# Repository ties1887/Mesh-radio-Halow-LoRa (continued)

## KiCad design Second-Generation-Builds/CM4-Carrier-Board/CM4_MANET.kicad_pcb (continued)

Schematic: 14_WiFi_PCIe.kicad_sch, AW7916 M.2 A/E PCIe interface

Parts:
C400: 100n / 16V; C_0603_1608Metric; MPN CL10B104KB8NNNC; LCSC C1591
J400: APCI0085-P005A / M.2 E-key socket; M2_E_KEY_APCI0085-P005A; MPN APCI0085-P005A; LCSC C7498138
R400, R401: 10k; R_0603_1608Metric; MPN 0603WAF1002T5E; LCSC C25804
R402: 10k / host-domain pullup; R_0603_1608Metric; MPN 0603WAF1002T5E; LCSC C25804
U400: 74LVC1G07SE-7; SOT-353_SC-70-5; MPN 74LVC1G07SE-7; LCSC C67531

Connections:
+3V3_CM4: R402.1; also elsewhere on the board
+3V3_WIFI: C400.1, J400.2 (3V3), J400.4 (3V3), J400.72 (3V3), J400.74 (3V3), R400.1, R401.1, U400.5 (VCC); also elsewhere on the board
CM4_PCIE_RST_N: U400.2 (A); also elsewhere on the board
GND: C400.2, J400.1 (GND), J400.7 (GND), J400.18 (GND), J400.33 (GND), J400.39 (GND), J400.45 (GND), J400.51 (GND), J400.57 (GND), J400.63 (GND), J400.69 (GND), J400.75 (GND), U400.3 (GND); also elsewhere on the board
PCIE_CLKREQ_N: J400.53 (CLKREQ_N), R402.2; also elsewhere on the board
PCIE_CLK_N: J400.49 (REFCLK_N); also elsewhere on the board
PCIE_CLK_P: J400.47 (REFCLK_P); also elsewhere on the board
PCIE_RX_N: J400.43 (CARD_TX_N); also elsewhere on the board
PCIE_RX_P: J400.41 (CARD_TX_P); also elsewhere on the board
PCIE_TX_N: J400.37 (CARD_RX_N); also elsewhere on the board
PCIE_TX_P: J400.35 (CARD_RX_P); also elsewhere on the board
WIFI_ENABLE_N: J400.56 (W_DISABLE1_N), R401.2
WIFI_PERST_N: J400.52 (PERST_N), R400.2, U400.4 (Y)

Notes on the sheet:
All four power contacts (2,4,72,74) carry WiFi supply; connector must support at least 0.75 A per power contact.
CM4 already includes PCIe TX and REFCLK coupling. Confirm coupling on AW7916 TX before PCB release.
AsiaRF drawing names TX/RX from card perspective: card RX pins35/37 receive CM4 TX; card TX41/43 drive CM4 RX.
Exact 1A/contact E-key socket suffix, physical mating and footprint are release blockers. Generic 0.5A sockets rejected.

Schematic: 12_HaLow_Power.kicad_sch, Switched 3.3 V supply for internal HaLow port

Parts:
C260: 1u / 10V input; C_0603_1608Metric; MPN CL10A105KB8NNNC; LCSC C15849
R260: 26.1k / 1%; R_0603_1608Metric; MPN FRC0603F2612TS; LCSC C2933182
R261, R262: 100k; R_0603_1608Metric; MPN 0603WAF1003T5E; LCSC C25803
R263: 10k / discharge; R_0603_1608Metric; MPN 0603WAF1002T5E; LCSC C25804
TP260: +3V3_HALOW; TestPoint_Pad_D1.5mm; JLCPCB Status EXCLUDE_FROM_JLCPCB_ASSEMBLY
U260: TPS2553DBVR; SOT-23-6; MPN TPS2553DBVR; LCSC C55266

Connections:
+3V3_AUX: C260.1, R262.1, U260.1 (IN); also elsewhere on the board
+3V3_HALOW: R263.1, TP260.1, U260.6 (OUT); also elsewhere on the board
GND: C260.2, R260.2, R261.2, R263.2, U260.2 (GND); also elsewhere on the board
HALOW_EN: R261.1, U260.3 (EN); also elsewhere on the board
HALOW_FAULT_N: R262.2, U260.4 (FAULT_N); also elsewhere on the board
HALOW_ILIM: R260.1, U260.5 (ILIM)

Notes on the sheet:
Internal hub port 1 enables the HaLow supply. This is a 3.3 V embedded-device rail, not external USB VBUS.
The whole module, including VDDIO and VDD_USB, powers from the same switched rail.
TPS2553 26.1k/1% limit: 908-1081mA, nominal 989mA; design reservation 0.6 A pending peak measurement.
RESET RC is on HaLow sheet. Check turn-off discharge/re-enumeration and 3.0 V minimum at module under peak load.

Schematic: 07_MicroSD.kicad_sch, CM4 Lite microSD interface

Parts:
C120: 10u / 10V; C_0805_2012Metric; MPN CL21A106KAYNNNE; LCSC C15850
C121: 100n / 16V; C_0603_1608Metric; MPN CL10B104KB8NNNC; LCSC C1591
J120: Molex 5033981892; SDCARD_MOLEX_503398-1892; MPN 5033981892; LCSC C428492
R120: 12k / 1%; R_0603_1608Metric; MPN FRC0603F1202TS; LCSC C2906989
U120: RT9742GGJ5; SOT-23-5; MPN RT9742GGJ5; LCSC C250547

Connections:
+3V3_CM4: C121.1, R120.1, U120.5 (VIN); also elsewhere on the board
GND: C120.2, C121.2, J120.6 (VSS), J120.11 (SHIELD), U120.2 (GND); also elsewhere on the board
SD_CLK: J120.5 (CLK); also elsewhere on the board
SD_CMD: J120.3 (CMD); also elsewhere on the board
SD_DAT0: J120.7 (DAT0); also elsewhere on the board
SD_DAT1: J120.8 (DAT1); also elsewhere on the board
SD_DAT2: J120.1 (DAT2); also elsewhere on the board
SD_DAT3: J120.2 (DAT3); also elsewhere on the board
SD_PWR_ON: R120.2, U120.4 (EN); also elsewhere on the board
SD_VDD: C120.1, J120.4 (VDD), U120.1 (VOUT)

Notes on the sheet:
Molex 503398-1892 socket and switched 3.3 V follow CM4IO reference.
Keep SD traces short with uninterrupted ground reference. 32 GB U3 card supplied separately.
No external pull-ups on SD data/CMD: use the CM4 reference arrangement. Card detect unused.
SD_PWR_ON has a pull-up so card is powered during boot. SD_VDD_OVERRIDE remains unconnected on CM4.

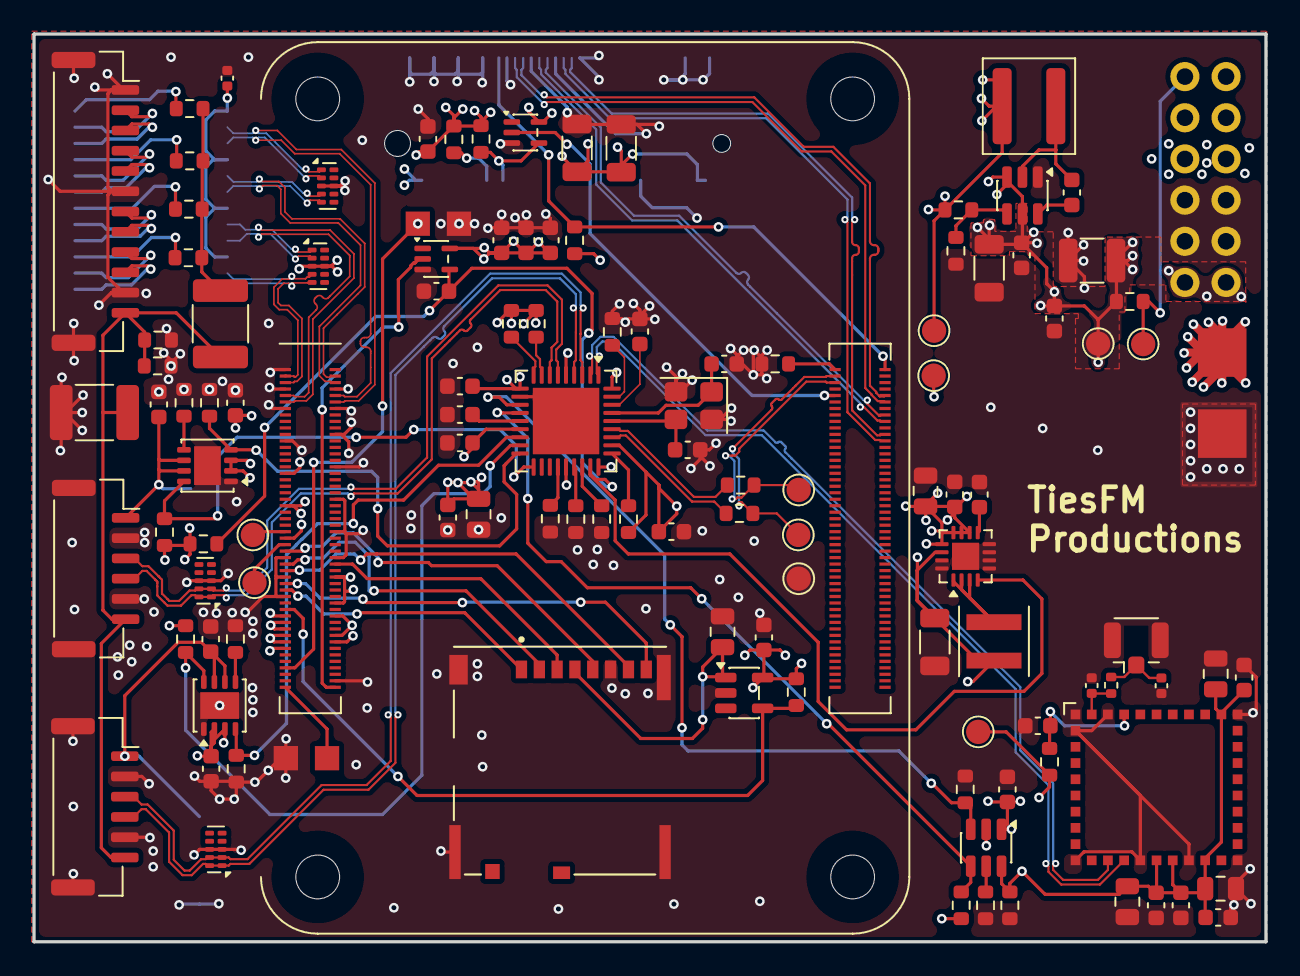
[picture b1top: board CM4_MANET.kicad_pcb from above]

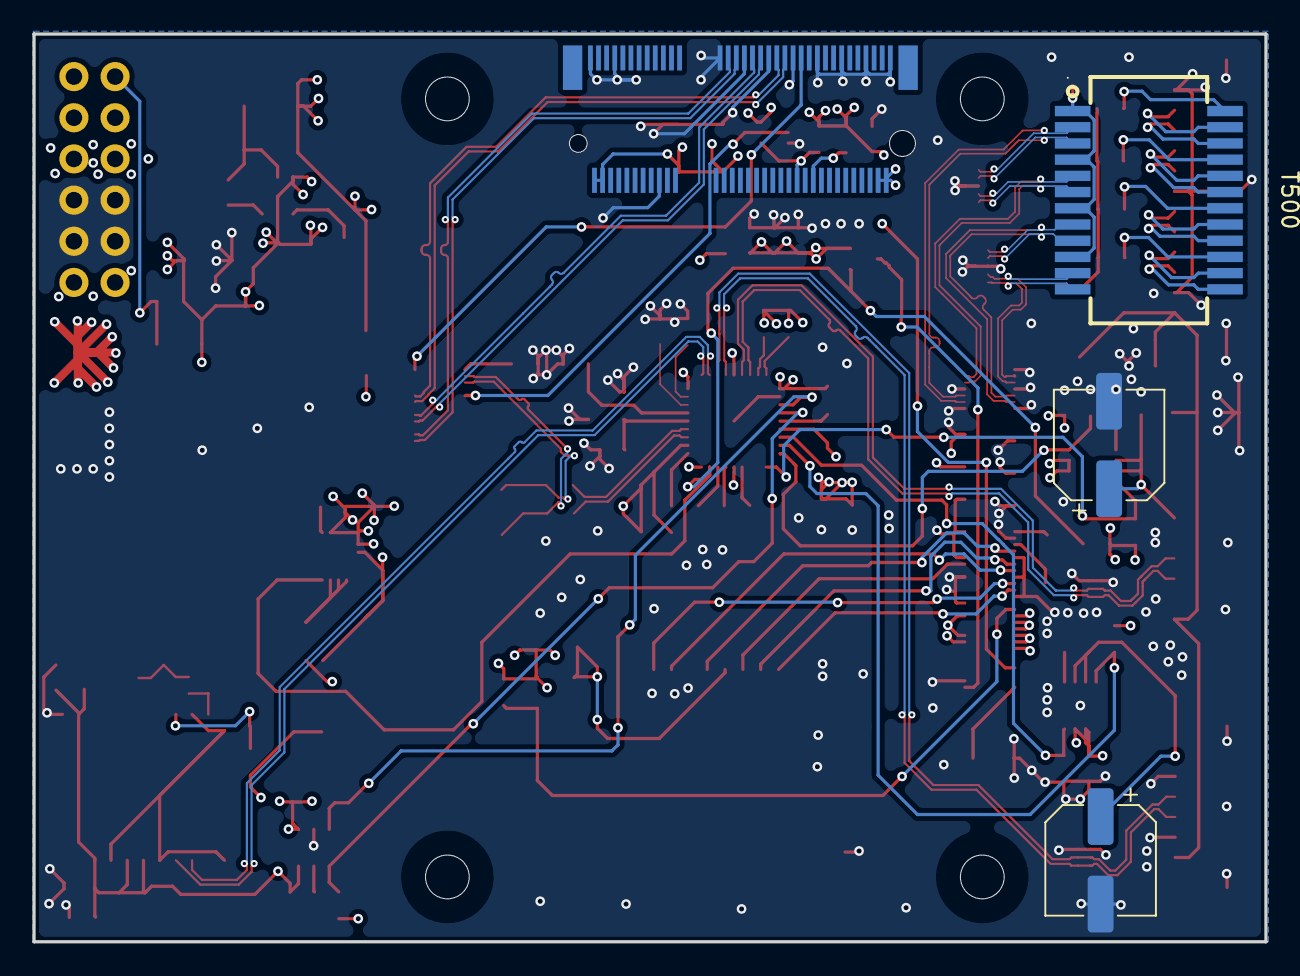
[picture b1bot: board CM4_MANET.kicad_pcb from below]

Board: 6 copper layers, 76.0 x 56.0 mm, 122 parts (4 on the bottom side), 96 nets.

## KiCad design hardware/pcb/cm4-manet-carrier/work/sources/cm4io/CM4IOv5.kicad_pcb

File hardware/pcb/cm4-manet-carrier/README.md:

# CM4 MANET — GitHub/Hermes-overdracht

Lees eerst HERMES-OVERDRACHT.md. Deze map wordt na de door de gebruiker gevraagde import in zijn GitHub-repository de centrale projectbron. Repository-URL en succesvolle upload zijn hier nog niet bekend. Deze overdracht uploadt zelf niets.

**Nieuwste proef: v0.8, AFGEKEURD. Referentie: v0.7, ook nog NIET geschikt voor productie. Geen gerouteerd carrierbord of vrijgegeven Gerbers.**

Alle historische versies, beschikbare lokale bronnen, modellen, scripts en projectnotities zijn behouden, behalve lokale caches, sessie-instellingen en interne Gitgeschiedenis. Het is geen volledige chat-export. Actuele aanwijzingen in dit README en HERMES-OVERDRACHT gaan vóór verouderde status-/Nextcloud-/routingstopteksten in historische documenten.

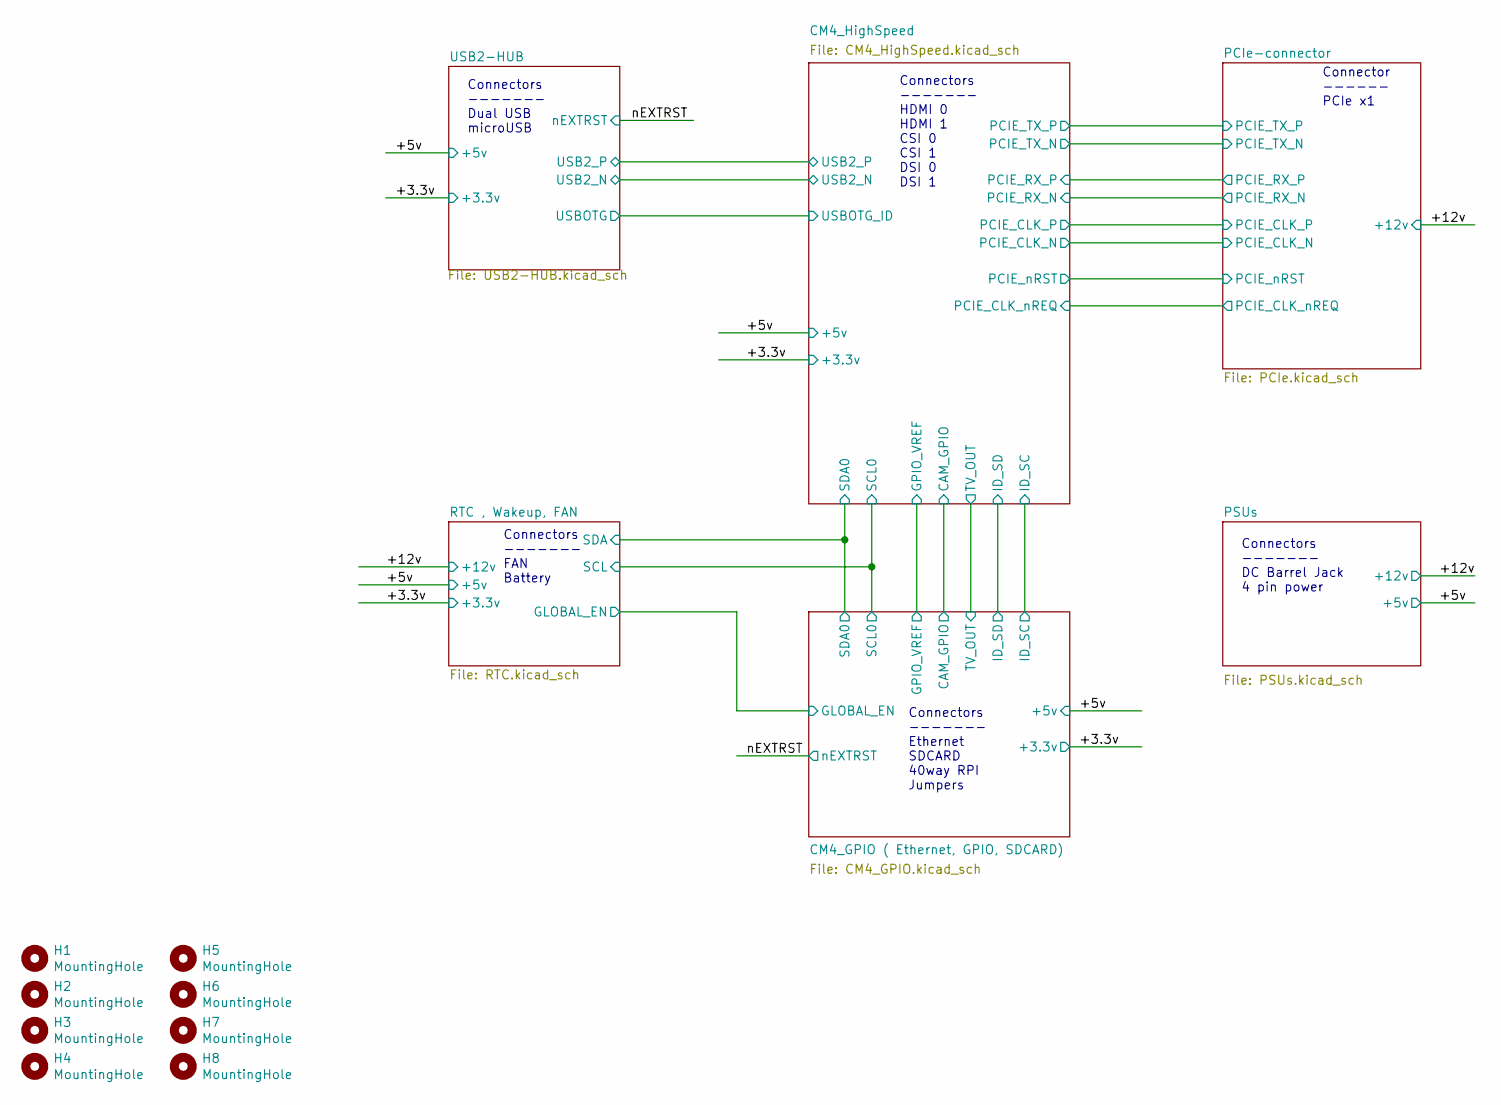
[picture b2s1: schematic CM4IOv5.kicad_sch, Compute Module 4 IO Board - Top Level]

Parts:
H1, H2, H3, H4, H5, H6, H7, H8: MountingHole; MountingHole_2.7mm_M2.5; Part Description M2.5 mounting hole

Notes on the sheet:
Connectors ------- FAN Battery
Connector ------ PCIe x1
Connectors ------- DC Barrel Jack 4 pin power
Connectors ------- Dual USB microUSB
Connectors ------- Ethernet SDCARD 40way RPI Jumpers
Connectors ------- HDMI 0 HDMI 1 CSI 0 CSI 1 DSI 0 DSI 1

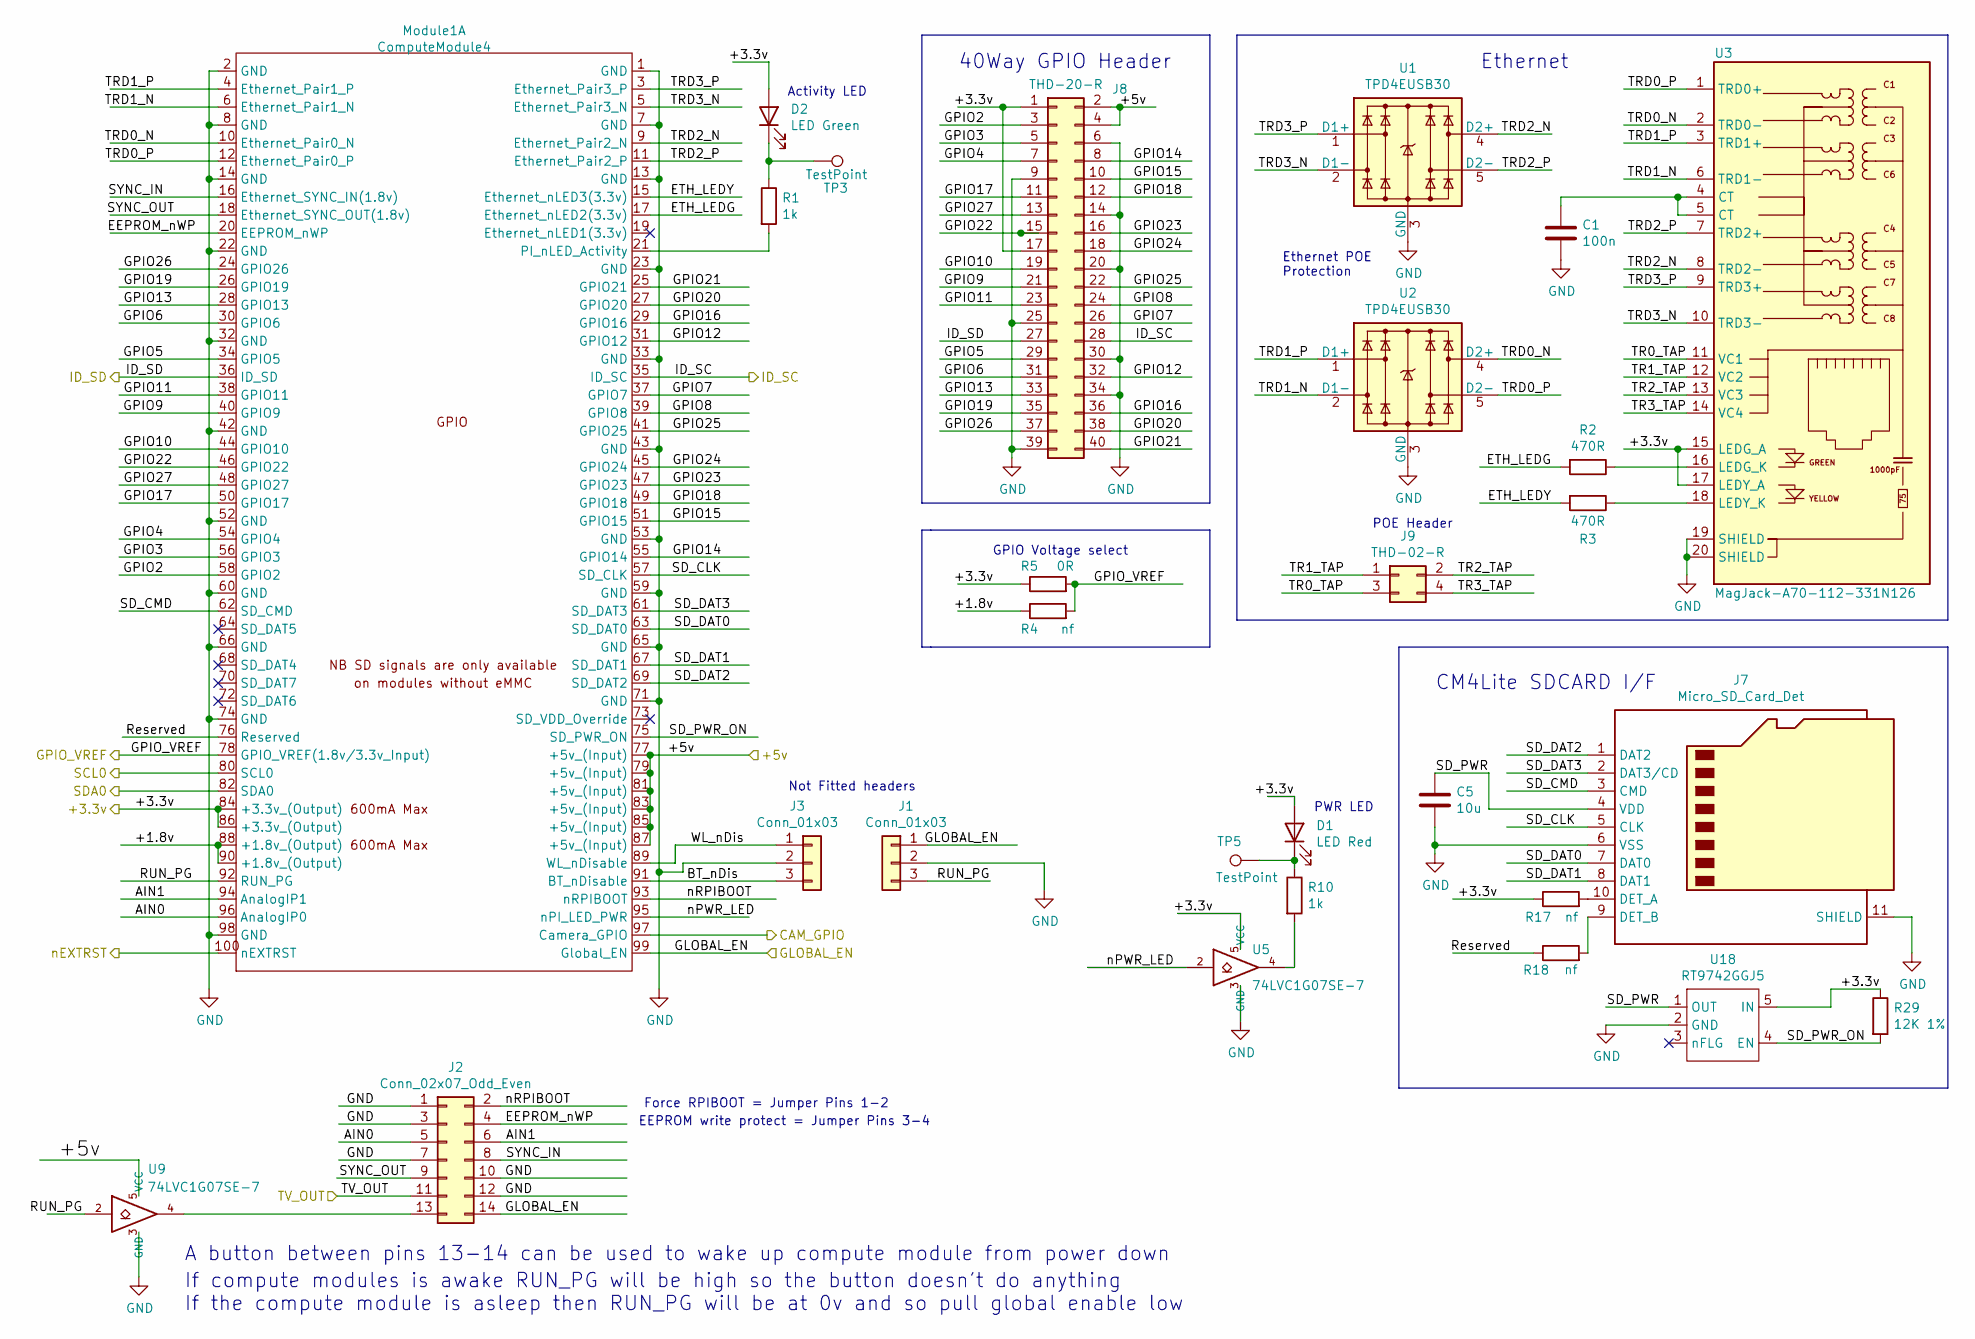
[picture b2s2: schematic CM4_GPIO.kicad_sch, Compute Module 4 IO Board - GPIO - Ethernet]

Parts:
C1: 100n; C_0402_1005Metric; Part Description 0.1uF 10% 16V Ceramic Capacitor X7R 040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
C5: 10u; C_0805_2012Metric; Part Description 10uF 10% 10V Ceramic Capacitor X7R 0805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
D1: LED Red; LED_0603_1608Metric; Part Description Red 620nm LED Indication - Discrete 2.2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
D2: LED Green; LED_0603_1608Metric; Part Description Green 572nm LED Indication - Discrete 2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
J1, J3: Conn_01x03; PinHeader_1x03_P2.54mm_Vertical; Part Description 3pin 0.1" connector
J2: Conn_02x07_Odd_Even; PinHeader_2x07_P2.54mm_Vertical; Part Description PinHeader_2x07_P2.54mm_Vertical
J7: Micro_SD_Card_Det; SDCARD_MOLEX_503398-1892; Part Description 9 (8 + 1) Position Card Connector micro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
J8: THD-20-R; PinHeader_2x20_P2.54mm_Vertical; Part Description PinHeader_2x20_P2.54mm_Vertical
J9: THD-02-R; PinHeader_2x02_P2.54mm_Vertical; Part Description PinHeader_2x02_P2.54mm_Vertical
Module1: ComputeModule4; Raspberry-Pi-4-Compute-Module; Part Description 100 Position Connector Receptacle, Cent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
R1, R10: 1k; R_0402_1005Metric; Part Description Resistor 1K M1005 1% 63mW
R2, R3: 470R; R_0402_1005Metric; Part Description Resistor 470R M1005 1% 63mW
R4: nf; R_0805_2012Metric_Pad1.15x1.40mm_HandSolder
R5: 0R; R_0805_2012Metric_Pad1.15x1.40mm_HandSolder; Part Description Resistor 0R M2012 5%
R17, R18: nf; R_0402_1005Metric; Part Description Resistor 1K M1005 1% 63mW
R29: 12K 1%; R_0402_1005Metric; Part Description Resistor 12K M1005 1% 63mW
TP3, TP5: TestPoint; TestPoint_Pad_2.0x2.0mm
U1, U2: TPD4EUSB30; USON-10_2.5x1.0mm_P0.5mm; Part Description Quad TVS diode for high speed signals (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
U3: MagJack-A70-112-331N126; TRJG0926HENL; Part Description Gigabit Ethernet Magjack
U5, U9: 74LVC1G07SE-7; SOT-353_SC-70-5; Part Description Buffer, Non-Inverting 1 Element 1 Bit p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
U18: RT9742GGJ5; SOT-23-5; Part Description Power Switch/Driver 1:1 N-Channel 1A TS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

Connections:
/+3.3v: D1.2 (A), D2.2 (A), J8.1, J8.17, Module1.84 (+3.3v_(Output)), Module1.86 (+3.3v_(Output)), R5.1, R17.1, R29.1, U3.15 (LEDG_A), U3.17 (LEDY_A), U5.5 (VCC), U18.5 (IN); also elsewhere on the board
/+5v: J8.2, J8.4, Module1.77 (+5v_(Input)), Module1.79 (+5v_(Input)), Module1.81 (+5v_(Input)), Module1.83 (+5v_(Input)), Module1.85 (+5v_(Input)), Module1.87 (+5v_(Input)), U9.5 (VCC); also elsewhere on the board
/CM4_GPIO ( Ethernet, GPIO, SDCARD)/+1.8v: Module1.88 (+1.8v_(Output)), Module1.90 (+1.8v_(Output)), R4.1
/CM4_GPIO ( Ethernet, GPIO, SDCARD)/AIN0: J2.5, Module1.96 (AnalogIP0)
/CM4_GPIO ( Ethernet, GPIO, SDCARD)/AIN1: J2.6, Module1.94 (AnalogIP1)
/CM4_GPIO ( Ethernet, GPIO, SDCARD)/BT_nDis: J3.3, Module1.91 (BT_nDisable)
/CM4_GPIO ( Ethernet, GPIO, SDCARD)/EEPROM_nWP: J2.4, Module1.20 (EEPROM_nWP)
/CM4_GPIO ( Ethernet, GPIO, SDCARD)/ETH_LEDG: Module1.17 (Ethernet_nLED2(3.3v)), R2.2
/CM4_GPIO ( Ethernet, GPIO, SDCARD)/ETH_LEDY: Module1.15 (Ethernet_nLED3(3.3v)), R3.2
/CM4_GPIO ( Ethernet, GPIO, SDCARD)/GLOBAL_EN: J1.1, J2.14, Module1.99 (Global_EN); also elsewhere on the board
/CM4_GPIO ( Ethernet, GPIO, SDCARD)/GPIO2: J8.3, Module1.58 (GPIO2)
/CM4_GPIO ( Ethernet, GPIO, SDCARD)/GPIO3: J8.5, Module1.56 (GPIO3)
/CM4_GPIO ( Ethernet, GPIO, SDCARD)/GPIO4: J8.7, Module1.54 (GPIO4)
/CM4_GPIO ( Ethernet, GPIO, SDCARD)/GPIO5: J8.29, Module1.34 (GPIO5)
/CM4_GPIO ( Ethernet, GPIO, SDCARD)/GPIO6: J8.31, Module1.30 (GPIO6)
/CM4_GPIO ( Ethernet, GPIO, SDCARD)/GPIO7: J8.26, Module1.37 (GPIO7)
/CM4_GPIO ( Ethernet, GPIO, SDCARD)/GPIO8: J8.24, Module1.39 (GPIO8)
/CM4_GPIO ( Ethernet, GPIO, SDCARD)/GPIO9: J8.21, Module1.40 (GPIO9)
/CM4_GPIO ( Ethernet, GPIO, SDCARD)/GPIO10: J8.19, Module1.44 (GPIO10)
/CM4_GPIO ( Ethernet, GPIO, SDCARD)/GPIO11: J8.23, Module1.38 (GPIO11)
/CM4_GPIO ( Ethernet, GPIO, SDCARD)/GPIO12: J8.32, Module1.31 (GPIO12)
/CM4_GPIO ( Ethernet, GPIO, SDCARD)/GPIO13: J8.33, Module1.28 (GPIO13)
/CM4_GPIO ( Ethernet, GPIO, SDCARD)/GPIO14: J8.8, Module1.55 (GPIO14)
/CM4_GPIO ( Ethernet, GPIO, SDCARD)/GPIO15: J8.10, Module1.51 (GPIO15)
/CM4_GPIO ( Ethernet, GPIO, SDCARD)/GPIO16: J8.36, Module1.29 (GPIO16)
/CM4_GPIO ( Ethernet, GPIO, SDCARD)/GPIO17: J8.11, Module1.50 (GPIO17)
/CM4_GPIO ( Ethernet, GPIO, SDCARD)/GPIO18: J8.12, Module1.49 (GPIO18)
/CM4_GPIO ( Ethernet, GPIO, SDCARD)/GPIO19: J8.35, Module1.26 (GPIO19)
/CM4_GPIO ( Ethernet, GPIO, SDCARD)/GPIO20: J8.38, Module1.27 (GPIO20)
/CM4_GPIO ( Ethernet, GPIO, SDCARD)/GPIO21: J8.40, Module1.25 (GPIO21)
/CM4_GPIO ( Ethernet, GPIO, SDCARD)/GPIO22: J8.15, Module1.46 (GPIO22)
/CM4_GPIO ( Ethernet, GPIO, SDCARD)/GPIO23: J8.16, Module1.47 (GPIO23)
/CM4_GPIO ( Ethernet, GPIO, SDCARD)/GPIO24: J8.18, Module1.45 (GPIO24)
/CM4_GPIO ( Ethernet, GPIO, SDCARD)/GPIO25: J8.22, Module1.41 (GPIO25)
/CM4_GPIO ( Ethernet, GPIO, SDCARD)/GPIO26: J8.37, Module1.24 (GPIO26)
/CM4_GPIO ( Ethernet, GPIO, SDCARD)/GPIO27: J8.13, Module1.48 (GPIO27)
/CM4_GPIO ( Ethernet, GPIO, SDCARD)/GPIO_VREF: Module1.78 (GPIO_VREF(1.8v/3.3v_Input)), R4.2, R5.2; also elsewhere on the board
/CM4_GPIO ( Ethernet, GPIO, SDCARD)/ID_SC: J8.28, Module1.35 (ID_SC); also elsewhere on the board
/CM4_GPIO ( Ethernet, GPIO, SDCARD)/ID_SD: J8.27, Module1.36 (ID_SD); also elsewhere on the board
/CM4_GPIO ( Ethernet, GPIO, SDCARD)/RUN_PG: J1.3, Module1.92 (RUN_PG), U9.2
/CM4_GPIO ( Ethernet, GPIO, SDCARD)/Reserved: Module1.76 (Reserved), R18.1
/CM4_GPIO ( Ethernet, GPIO, SDCARD)/SD_CLK: J7.5 (CLK), Module1.57 (SD_CLK)
/CM4_GPIO ( Ethernet, GPIO, SDCARD)/SD_CMD: J7.3 (CMD), Module1.62 (SD_CMD)
/CM4_GPIO ( Ethernet, GPIO, SDCARD)/SD_DAT0: J7.7 (DAT0), Module1.63 (SD_DAT0)
/CM4_GPIO ( Ethernet, GPIO, SDCARD)/SD_DAT1: J7.8 (DAT1), Module1.67 (SD_DAT1)
/CM4_GPIO ( Ethernet, GPIO, SDCARD)/SD_DAT2: J7.1 (DAT2), Module1.69 (SD_DAT2)
/CM4_GPIO ( Ethernet, GPIO, SDCARD)/SD_DAT3: J7.2 (DAT3/CD), Module1.61 (SD_DAT3)
/CM4_GPIO ( Ethernet, GPIO, SDCARD)/SD_PWR: C5.1, J7.4 (VDD), U18.1 (OUT)
/CM4_GPIO ( Ethernet, GPIO, SDCARD)/SD_PWR_ON: Module1.75 (SD_PWR_ON), R29.2, U18.4 (EN)
/CM4_GPIO ( Ethernet, GPIO, SDCARD)/SYNC_IN: J2.8, Module1.16 (Ethernet_SYNC_IN(1.8v))
/CM4_GPIO ( Ethernet, GPIO, SDCARD)/SYNC_OUT: J2.9, Module1.18 (Ethernet_SYNC_OUT(1.8v))
/CM4_GPIO ( Ethernet, GPIO, SDCARD)/TR0_TAP: J9.3, U3.11 (VC1)
/CM4_GPIO ( Ethernet, GPIO, SDCARD)/TR1_TAP: J9.1, U3.12 (VC2)
/CM4_GPIO ( Ethernet, GPIO, SDCARD)/TR2_TAP: J9.2, U3.13 (VC3)
/CM4_GPIO ( Ethernet, GPIO, SDCARD)/TR3_TAP: J9.4, U3.14 (VC4)
/CM4_GPIO ( Ethernet, GPIO, SDCARD)/TRD0_N: Module1.10 (Ethernet_Pair0_N), U2.4 (D2+), U2.7, U3.2 (TRD0-)
/CM4_GPIO ( Ethernet, GPIO, SDCARD)/TRD0_P: Module1.12 (Ethernet_Pair0_P), U2.5 (D2-), U2.6, U3.1 (TRD0+)
/CM4_GPIO ( Ethernet, GPIO, SDCARD)/TRD1_N: Module1.6 (Ethernet_Pair1_N), U2.2 (D1-), U2.9, U3.6 (TRD1-)
/CM4_GPIO ( Ethernet, GPIO, SDCARD)/TRD1_P: Module1.4 (Ethernet_Pair1_P), U2.1 (D1+), U2.10, U3.3 (TRD1+)
/CM4_GPIO ( Ethernet, GPIO, SDCARD)/TRD2_N: Module1.9 (Ethernet_Pair2_N), U1.4 (D2+), U1.7, U3.8 (TRD2-)
/CM4_GPIO ( Ethernet, GPIO, SDCARD)/TRD2_P: Module1.11 (Ethernet_Pair2_P), U1.5 (D2-), U1.6, U3.7 (TRD2+)
/CM4_GPIO ( Ethernet, GPIO, SDCARD)/TRD3_N: Module1.5 (Ethernet_Pair3_N), U1.2 (D1-), U1.9, U3.10 (TRD3-)
/CM4_GPIO ( Ethernet, GPIO, SDCARD)/TRD3_P: Module1.3 (Ethernet_Pair3_P), U1.1 (D1+), U1.10, U3.9 (TRD3+)
/CM4_GPIO ( Ethernet, GPIO, SDCARD)/TV_OUT: J2.11; also elsewhere on the board
/CM4_GPIO ( Ethernet, GPIO, SDCARD)/WL_nDis: J3.1, Module1.89 (WL_nDisable)
/CM4_GPIO ( Ethernet, GPIO, SDCARD)/nPWR_LED: Module1.95 (nPI_LED_PWR), U5.2
/CM4_GPIO ( Ethernet, GPIO, SDCARD)/nRPIBOOT: J2.2, Module1.93 (nRPIBOOT)
/CM4_HighSpeed/CAM_GPIO: Module1.97 (Camera_GPIO); also elsewhere on the board
/CM4_HighSpeed/SCL0: Module1.80 (SCL0); also elsewhere on the board
/CM4_HighSpeed/SDA0: Module1.82 (SDA0); also elsewhere on the board
/nEXTRST: Module1.100 (nEXTRST); also elsewhere on the board
GND: C1.2, C5.2, J1.2, J2.1, J2.3, J2.7, J2.10, J2.12, J3.2, J7.6 (VSS), J7.11 (SHIELD), J8.6, J8.9, J8.14, J8.20, J8.25, J8.30, J8.34, J8.39, Module1.1 (GND), Module1.2 (GND), Module1.7 (GND), Module1.8 (GND), Module1.13 (GND), Module1.14 (GND), Module1.22 (GND), Module1.23 (GND), Module1.32 (GND), Module1.33 (GND), Module1.42 (GND), Module1.43 (GND), Module1.52 (GND), Module1.53 (GND), Module1.59 (GND), Module1.60 (GND), Module1.65 (GND), Module1.66 (GND), Module1.71 (GND), Module1.74 (GND), Module1.98 (GND), U1.3 (GND), U1.8 (GND), U2.3 (GND), U2.8 (GND), U3.19 (SHIELD), U3.20 (SHIELD), U5.3 (GND), U9.3 (GND), U18.2 (GND); also elsewhere on the board
unnamed: C1.1, U3.4 (CT), U3.5 (CT)
unnamed: D1.1 (K), R10.1, TP5.1
unnamed: D2.1 (K), R1.1, TP3.1
unnamed: J2.13, U9.4
unnamed: J7.9 (DET_B), R18.2
unnamed: J7.10 (DET_A), R17.2
unnamed: Module1.21 (PI_nLED_Activity), R1.2
unnamed: R2.1, U3.16 (LEDG_K)
unnamed: R3.1, U3.18 (LEDY_K)
unnamed: R10.2, U5.4

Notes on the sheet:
PWR LED
Ethernet POE Protection
40Way GPIO Header
CM4Lite SDCARD I/F
GPIO Voltage select
Ethernet
Activity LED
EEPROM write protect = Jumper Pins 3-4
Not Fitted headers
A button between pins 13-14 can be used to wake up compute module from power down
If compute modules is awake RUN_PG will be high so the button doesn't do anything If the compute module is asleep then RUN_PG will be at 0v and so pull global enable low
Force RPIBOOT = Jumper Pins 1-2
POE Header

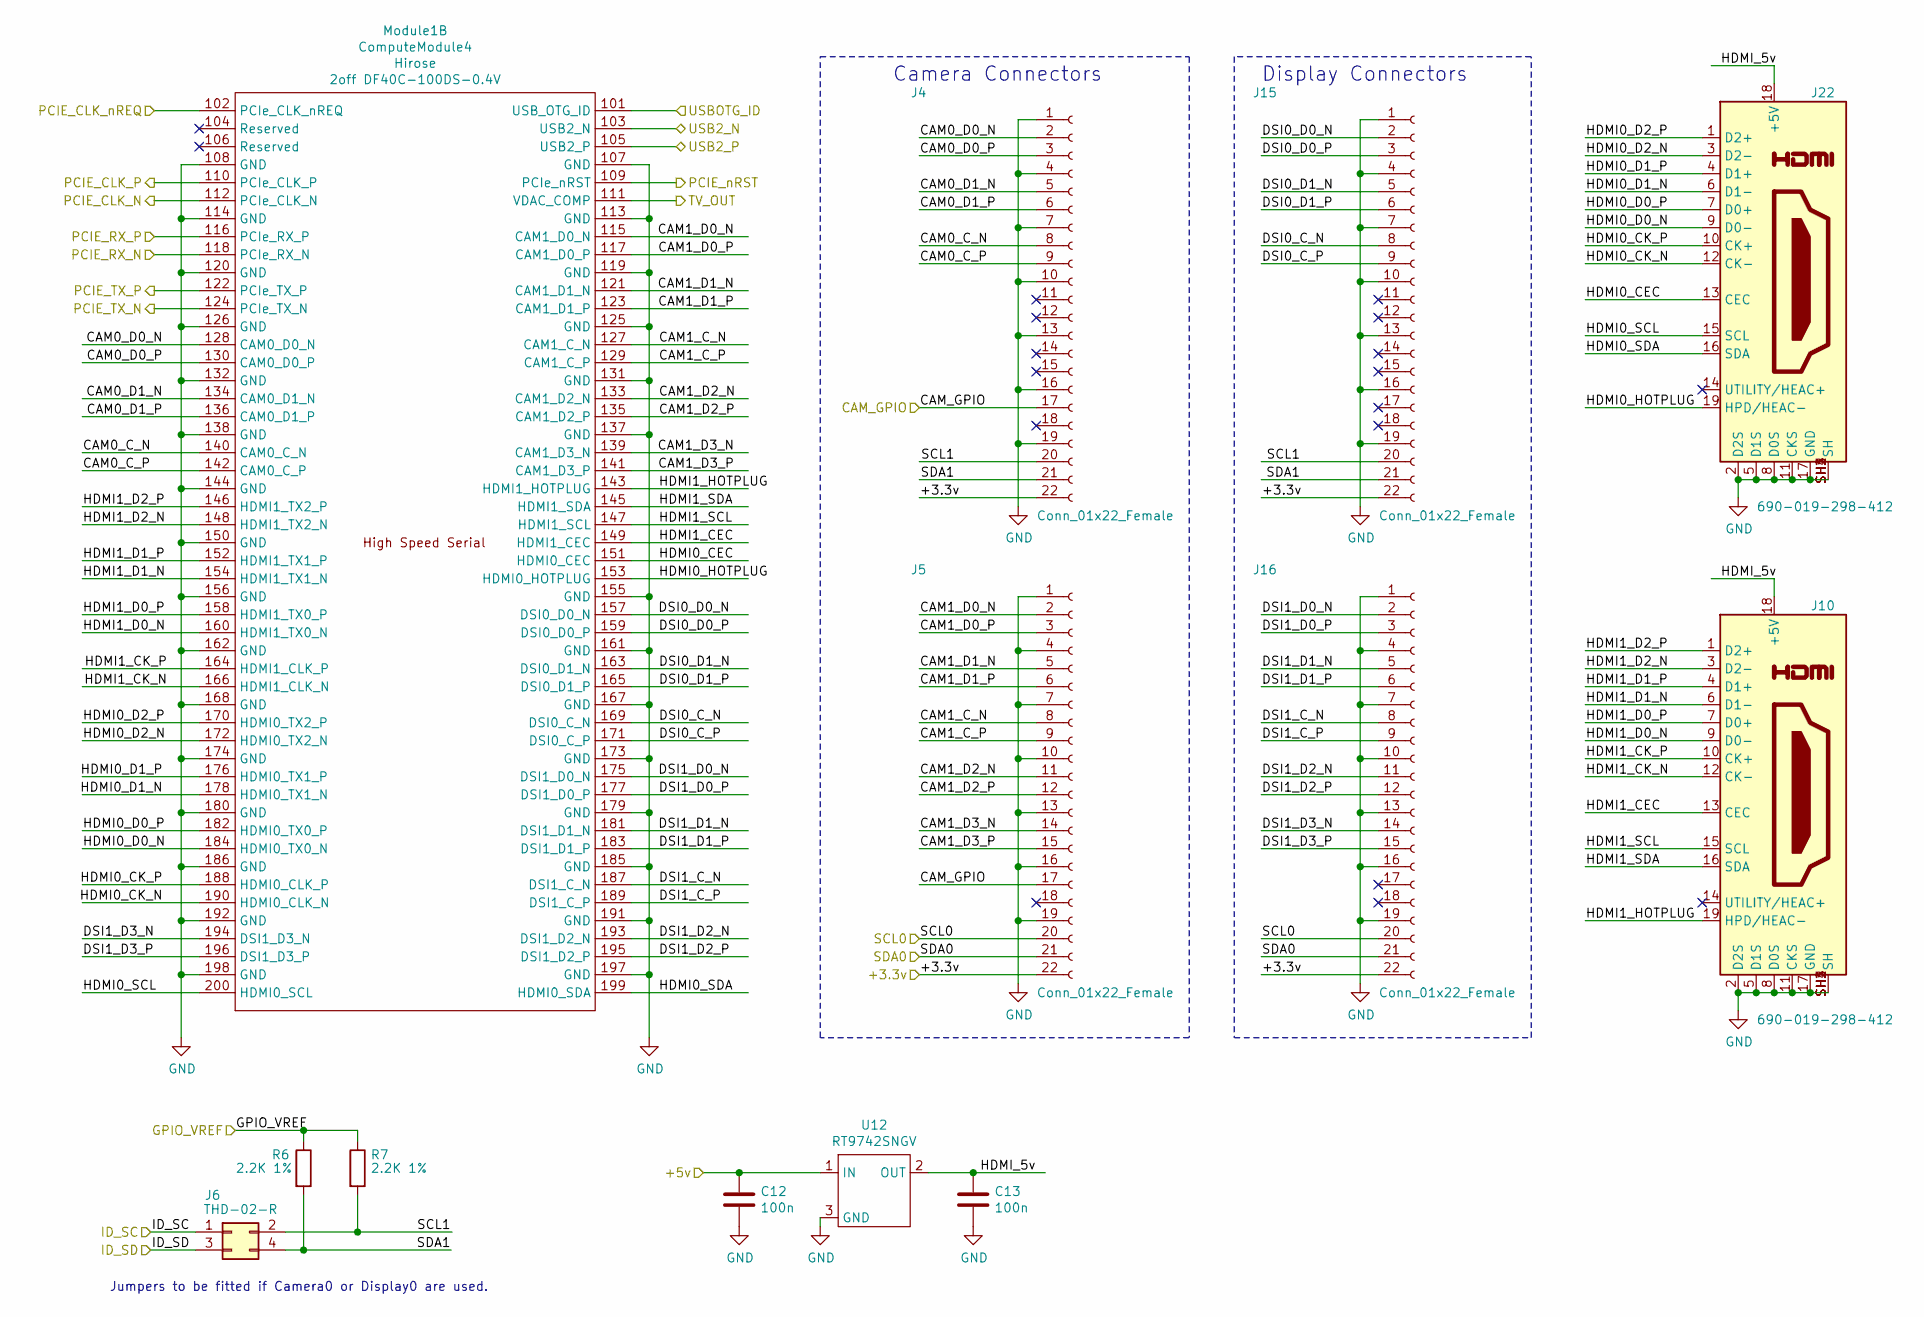
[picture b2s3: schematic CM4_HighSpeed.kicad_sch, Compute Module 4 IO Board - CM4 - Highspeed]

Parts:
C12, C13: 100n; C_0402_1005Metric; Part Description 0.1uF 10% 16V Ceramic Capacitor X7R 040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
J4, J5, J15, J16: Conn_01x22_Female; Hirose_FH12-22S-0.5SH_1x22-1MP_P0.50mm_Horizontal; Part Description 22 Position FFC, FPC Connector Contacts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
J6: THD-02-R; PinHeader_2x02_P2.54mm_Vertical; Part Description PinHeader_2x02_P2.54mm_Vertical
J10, J22: 690-019-298-412; EDAC 690-019-298-412; Part Description HDMI Connector, Right Angle, 19 Contact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
Module1: ComputeModule4; Raspberry-Pi-4-Compute-Module; Part Description 100 Position Connector Receptacle, Cent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
R6, R7: 2.2K 1%; R_0402_1005Metric; Part Description Resistor 2.2K M1005 1% 63mW
U12: RT9742SNGV; SOT-23; Part Description Power Switch/Driver 1:1 N-Channel 500mA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

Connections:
/+3.3v: J4.22, J5.22, J15.22, J16.22; also elsewhere on the board
/+5v: C12.1, U12.1 (IN); also elsewhere on the board
/CM4_GPIO ( Ethernet, GPIO, SDCARD)/GPIO_VREF: R6.1, R7.1; also elsewhere on the board
/CM4_GPIO ( Ethernet, GPIO, SDCARD)/ID_SC: J6.1; also elsewhere on the board
/CM4_GPIO ( Ethernet, GPIO, SDCARD)/ID_SD: J6.3; also elsewhere on the board
/CM4_GPIO ( Ethernet, GPIO, SDCARD)/TV_OUT: Module1.111 (VDAC_COMP); also elsewhere on the board
/CM4_HighSpeed/CAM0_C_N: J4.8, Module1.140 (CAM0_C_N)
/CM4_HighSpeed/CAM0_C_P: J4.9, Module1.142 (CAM0_C_P)
/CM4_HighSpeed/CAM0_D0_N: J4.2, Module1.128 (CAM0_D0_N)
/CM4_HighSpeed/CAM0_D0_P: J4.3, Module1.130 (CAM0_D0_P)
/CM4_HighSpeed/CAM0_D1_N: J4.5, Module1.134 (CAM0_D1_N)
/CM4_HighSpeed/CAM0_D1_P: J4.6, Module1.136 (CAM0_D1_P)
/CM4_HighSpeed/CAM1_C_N: J5.8, Module1.127 (CAM1_C_N)
/CM4_HighSpeed/CAM1_C_P: J5.9, Module1.129 (CAM1_C_P)
/CM4_HighSpeed/CAM1_D0_N: J5.2, Module1.115 (CAM1_D0_N)
/CM4_HighSpeed/CAM1_D0_P: J5.3, Module1.117 (CAM1_D0_P)
/CM4_HighSpeed/CAM1_D1_N: J5.5, Module1.121 (CAM1_D1_N)
/CM4_HighSpeed/CAM1_D1_P: J5.6, Module1.123 (CAM1_D1_P)
/CM4_HighSpeed/CAM1_D2_N: J5.11, Module1.133 (CAM1_D2_N)
/CM4_HighSpeed/CAM1_D2_P: J5.12, Module1.135 (CAM1_D2_P)
/CM4_HighSpeed/CAM1_D3_N: J5.14, Module1.139 (CAM1_D3_N)
/CM4_HighSpeed/CAM1_D3_P: J5.15, Module1.141 (CAM1_D3_P)
/CM4_HighSpeed/CAM_GPIO: J4.17, J5.17; also elsewhere on the board
/CM4_HighSpeed/DSI0_C_N: J15.8, Module1.169 (DSI0_C_N)
/CM4_HighSpeed/DSI0_C_P: J15.9, Module1.171 (DSI0_C_P)
/CM4_HighSpeed/DSI0_D0_N: J15.2, Module1.157 (DSI0_D0_N)
/CM4_HighSpeed/DSI0_D0_P: J15.3, Module1.159 (DSI0_D0_P)
/CM4_HighSpeed/DSI0_D1_N: J15.5, Module1.163 (DSI0_D1_N)
/CM4_HighSpeed/DSI0_D1_P: J15.6, Module1.165 (DSI0_D1_P)
/CM4_HighSpeed/DSI1_C_N: J16.8, Module1.187 (DSI1_C_N)
/CM4_HighSpeed/DSI1_C_P: J16.9, Module1.189 (DSI1_C_P)
/CM4_HighSpeed/DSI1_D0_N: J16.2, Module1.175 (DSI1_D0_N)
/CM4_HighSpeed/DSI1_D0_P: J16.3, Module1.177 (DSI1_D0_P)
/CM4_HighSpeed/DSI1_D1_N: J16.5, Module1.181 (DSI1_D1_N)
/CM4_HighSpeed/DSI1_D1_P: J16.6, Module1.183 (DSI1_D1_P)
/CM4_HighSpeed/DSI1_D2_N: J16.11, Module1.193 (DSI1_D2_N)
/CM4_HighSpeed/DSI1_D2_P: J16.12, Module1.195 (DSI1_D2_P)
/CM4_HighSpeed/DSI1_D3_N: J16.14, Module1.194 (DSI1_D3_N)
/CM4_HighSpeed/DSI1_D3_P: J16.15, Module1.196 (DSI1_D3_P)
/CM4_HighSpeed/HDMI0_CEC: J22.13 (CEC), Module1.151 (HDMI0_CEC)
/CM4_HighSpeed/HDMI0_CK_N: J22.12 (CK-), Module1.190 (HDMI0_CLK_N)
/CM4_HighSpeed/HDMI0_CK_P: J22.10 (CK+), Module1.188 (HDMI0_CLK_P)
/CM4_HighSpeed/HDMI0_D0_N: J22.9 (D0-), Module1.184 (HDMI0_TX0_N)
/CM4_HighSpeed/HDMI0_D0_P: J22.7 (D0+), Module1.182 (HDMI0_TX0_P)
/CM4_HighSpeed/HDMI0_D1_N: J22.6 (D1-), Module1.178 (HDMI0_TX1_N)
/CM4_HighSpeed/HDMI0_D1_P: J22.4 (D1+), Module1.176 (HDMI0_TX1_P)
/CM4_HighSpeed/HDMI0_D2_N: J22.3 (D2-), Module1.172 (HDMI0_TX2_N)
/CM4_HighSpeed/HDMI0_D2_P: J22.1 (D2+), Module1.170 (HDMI0_TX2_P)
/CM4_HighSpeed/HDMI0_HOTPLUG: J22.19 (HPD/HEAC-), Module1.153 (HDMI0_HOTPLUG)
/CM4_HighSpeed/HDMI0_SCL: J22.15 (SCL), Module1.200 (HDMI0_SCL)
/CM4_HighSpeed/HDMI0_SDA: J22.16 (SDA), Module1.199 (HDMI0_SDA)
/CM4_HighSpeed/HDMI1_CEC: J10.13 (CEC), Module1.149 (HDMI1_CEC)
/CM4_HighSpeed/HDMI1_CK_N: J10.12 (CK-), Module1.166 (HDMI1_CLK_N)
/CM4_HighSpeed/HDMI1_CK_P: J10.10 (CK+), Module1.164 (HDMI1_CLK_P)
/CM4_HighSpeed/HDMI1_D0_N: J10.9 (D0-), Module1.160 (HDMI1_TX0_N)
/CM4_HighSpeed/HDMI1_D0_P: J10.7 (D0+), Module1.158 (HDMI1_TX0_P)
/CM4_HighSpeed/HDMI1_D1_N: J10.6 (D1-), Module1.154 (HDMI1_TX1_N)
/CM4_HighSpeed/HDMI1_D1_P: J10.4 (D1+), Module1.152 (HDMI1_TX1_P)
/CM4_HighSpeed/HDMI1_D2_N: J10.3 (D2-), Module1.148 (HDMI1_TX2_N)
/CM4_HighSpeed/HDMI1_D2_P: J10.1 (D2+), Module1.146 (HDMI1_TX2_P)
/CM4_HighSpeed/HDMI1_HOTPLUG: J10.19 (HPD/HEAC-), Module1.143 (HDMI1_HOTPLUG)
/CM4_HighSpeed/HDMI1_SCL: J10.15 (SCL), Module1.147 (HDMI1_SCL)
/CM4_HighSpeed/HDMI1_SDA: J10.16 (SDA), Module1.145 (HDMI1_SDA)
/CM4_HighSpeed/HDMI_5v: C13.1, J10.18 (+5V), J22.18 (+5V), U12.2 (OUT)
/CM4_HighSpeed/PCIE_CLK_N: Module1.112 (PCIe_CLK_N); also elsewhere on the board
/CM4_HighSpeed/PCIE_CLK_P: Module1.110 (PCIe_CLK_P); also elsewhere on the board
/CM4_HighSpeed/PCIE_CLK_nREQ: Module1.102 (PCIe_CLK_nREQ); also elsewhere on the board
/CM4_HighSpeed/PCIE_RX_N: Module1.118 (PCIe_RX_N); also elsewhere on the board
/CM4_HighSpeed/PCIE_RX_P: Module1.116 (PCIe_RX_P); also elsewhere on the board
/CM4_HighSpeed/PCIE_TX_N: Module1.124 (PCIe_TX_N); also elsewhere on the board
/CM4_HighSpeed/PCIE_TX_P: Module1.122 (PCIe_TX_P); also elsewhere on the board
/CM4_HighSpeed/PCIE_nRST: Module1.109 (PCIe_nRST); also elsewhere on the board
/CM4_HighSpeed/SCL0: J5.20, J16.20; also elsewhere on the board
/CM4_HighSpeed/SCL1: J4.20, J6.2, J15.20, R7.2
/CM4_HighSpeed/SDA0: J5.21, J16.21; also elsewhere on the board
/CM4_HighSpeed/SDA1: J4.21, J6.4, J15.21, R6.2
/CM4_HighSpeed/USB2_N: Module1.103 (USB2_N); also elsewhere on the board
/CM4_HighSpeed/USB2_P: Module1.105 (USB2_P); also elsewhere on the board
/CM4_HighSpeed/USBOTG_ID: Module1.101 (USB_OTG_ID); also elsewhere on the board
GND: C12.2, C13.2, J4.1, J4.4, J4.7, J4.10, J4.13, J4.16, J4.19, J5.1, J5.4, J5.7, J5.10, J5.13, J5.16, J5.19, J10.2 (D2S), J10.5 (D1S), J10.8 (D0S), J10.11 (CKS), J10.17 (GND), J10.SH1 (SH), J10.SH2 (SH), J10.SH3 (SH), J10.SH4 (SH), J15.1, J15.4, J15.7, J15.10, J15.13, J15.16, J15.19, J16.1, J16.4, J16.7, J16.10, J16.13, J16.16, J16.19, J22.2 (D2S), J22.5 (D1S), J22.8 (D0S), J22.11 (CKS), J22.17 (GND), J22.SH1 (SH), J22.SH2 (SH), J22.SH3 (SH), J22.SH4 (SH), Module1.107 (GND), Module1.108 (GND), Module1.113 (GND), Module1.114 (GND), Module1.119 (GND), Module1.120 (GND), Module1.125 (GND), Module1.126 (GND), Module1.131 (GND), Module1.132 (GND), Module1.137 (GND), Module1.138 (GND), Module1.144 (GND), Module1.150 (GND), Module1.155 (GND), Module1.156 (GND), Module1.161 (GND), Module1.162 (GND), Module1.167 (GND), Module1.168 (GND), Module1.173 (GND), Module1.174 (GND), Module1.179 (GND), Module1.180 (GND), Module1.185 (GND), Module1.186 (GND), Module1.191 (GND), Module1.192 (GND), Module1.197 (GND), Module1.198 (GND), U12.3 (GND); also elsewhere on the board

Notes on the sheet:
Jumpers to be fitted if Camera0 or Display0 are used.
Camera Connectors
Display Connectors
